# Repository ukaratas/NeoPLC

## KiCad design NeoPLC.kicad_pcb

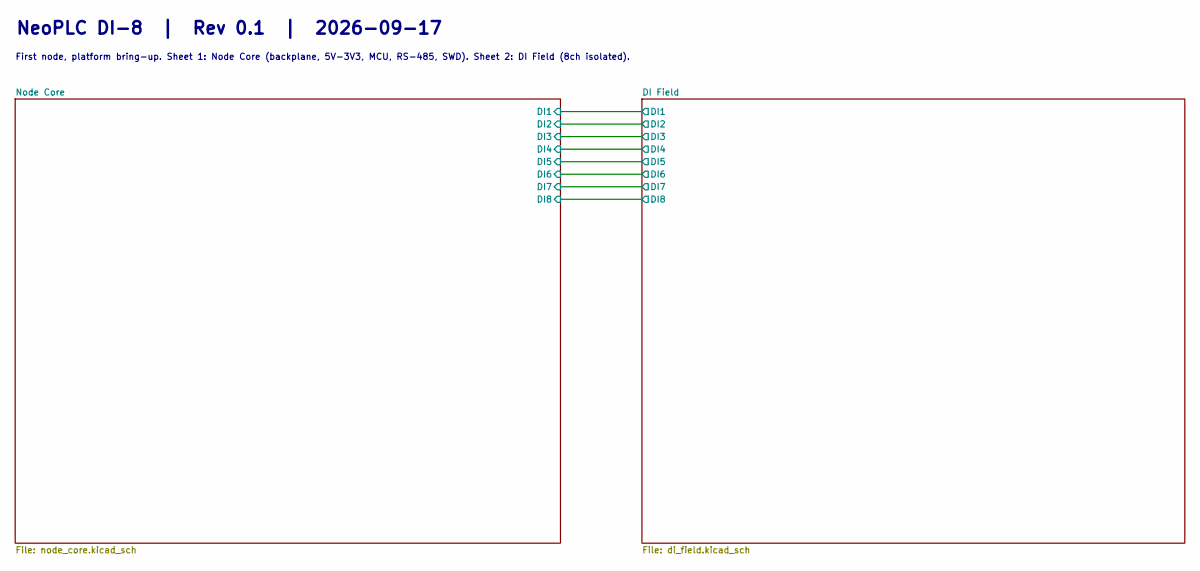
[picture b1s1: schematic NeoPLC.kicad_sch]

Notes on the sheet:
NeoPLC DI-8 | Rev 0.1 | 2026-09-17
First node, platform bring-up. Sheet 1: Node Core (backplane, 5V-3V3, MCU, RS-485, SWD). Sheet 2: DI Field (8ch isolated).

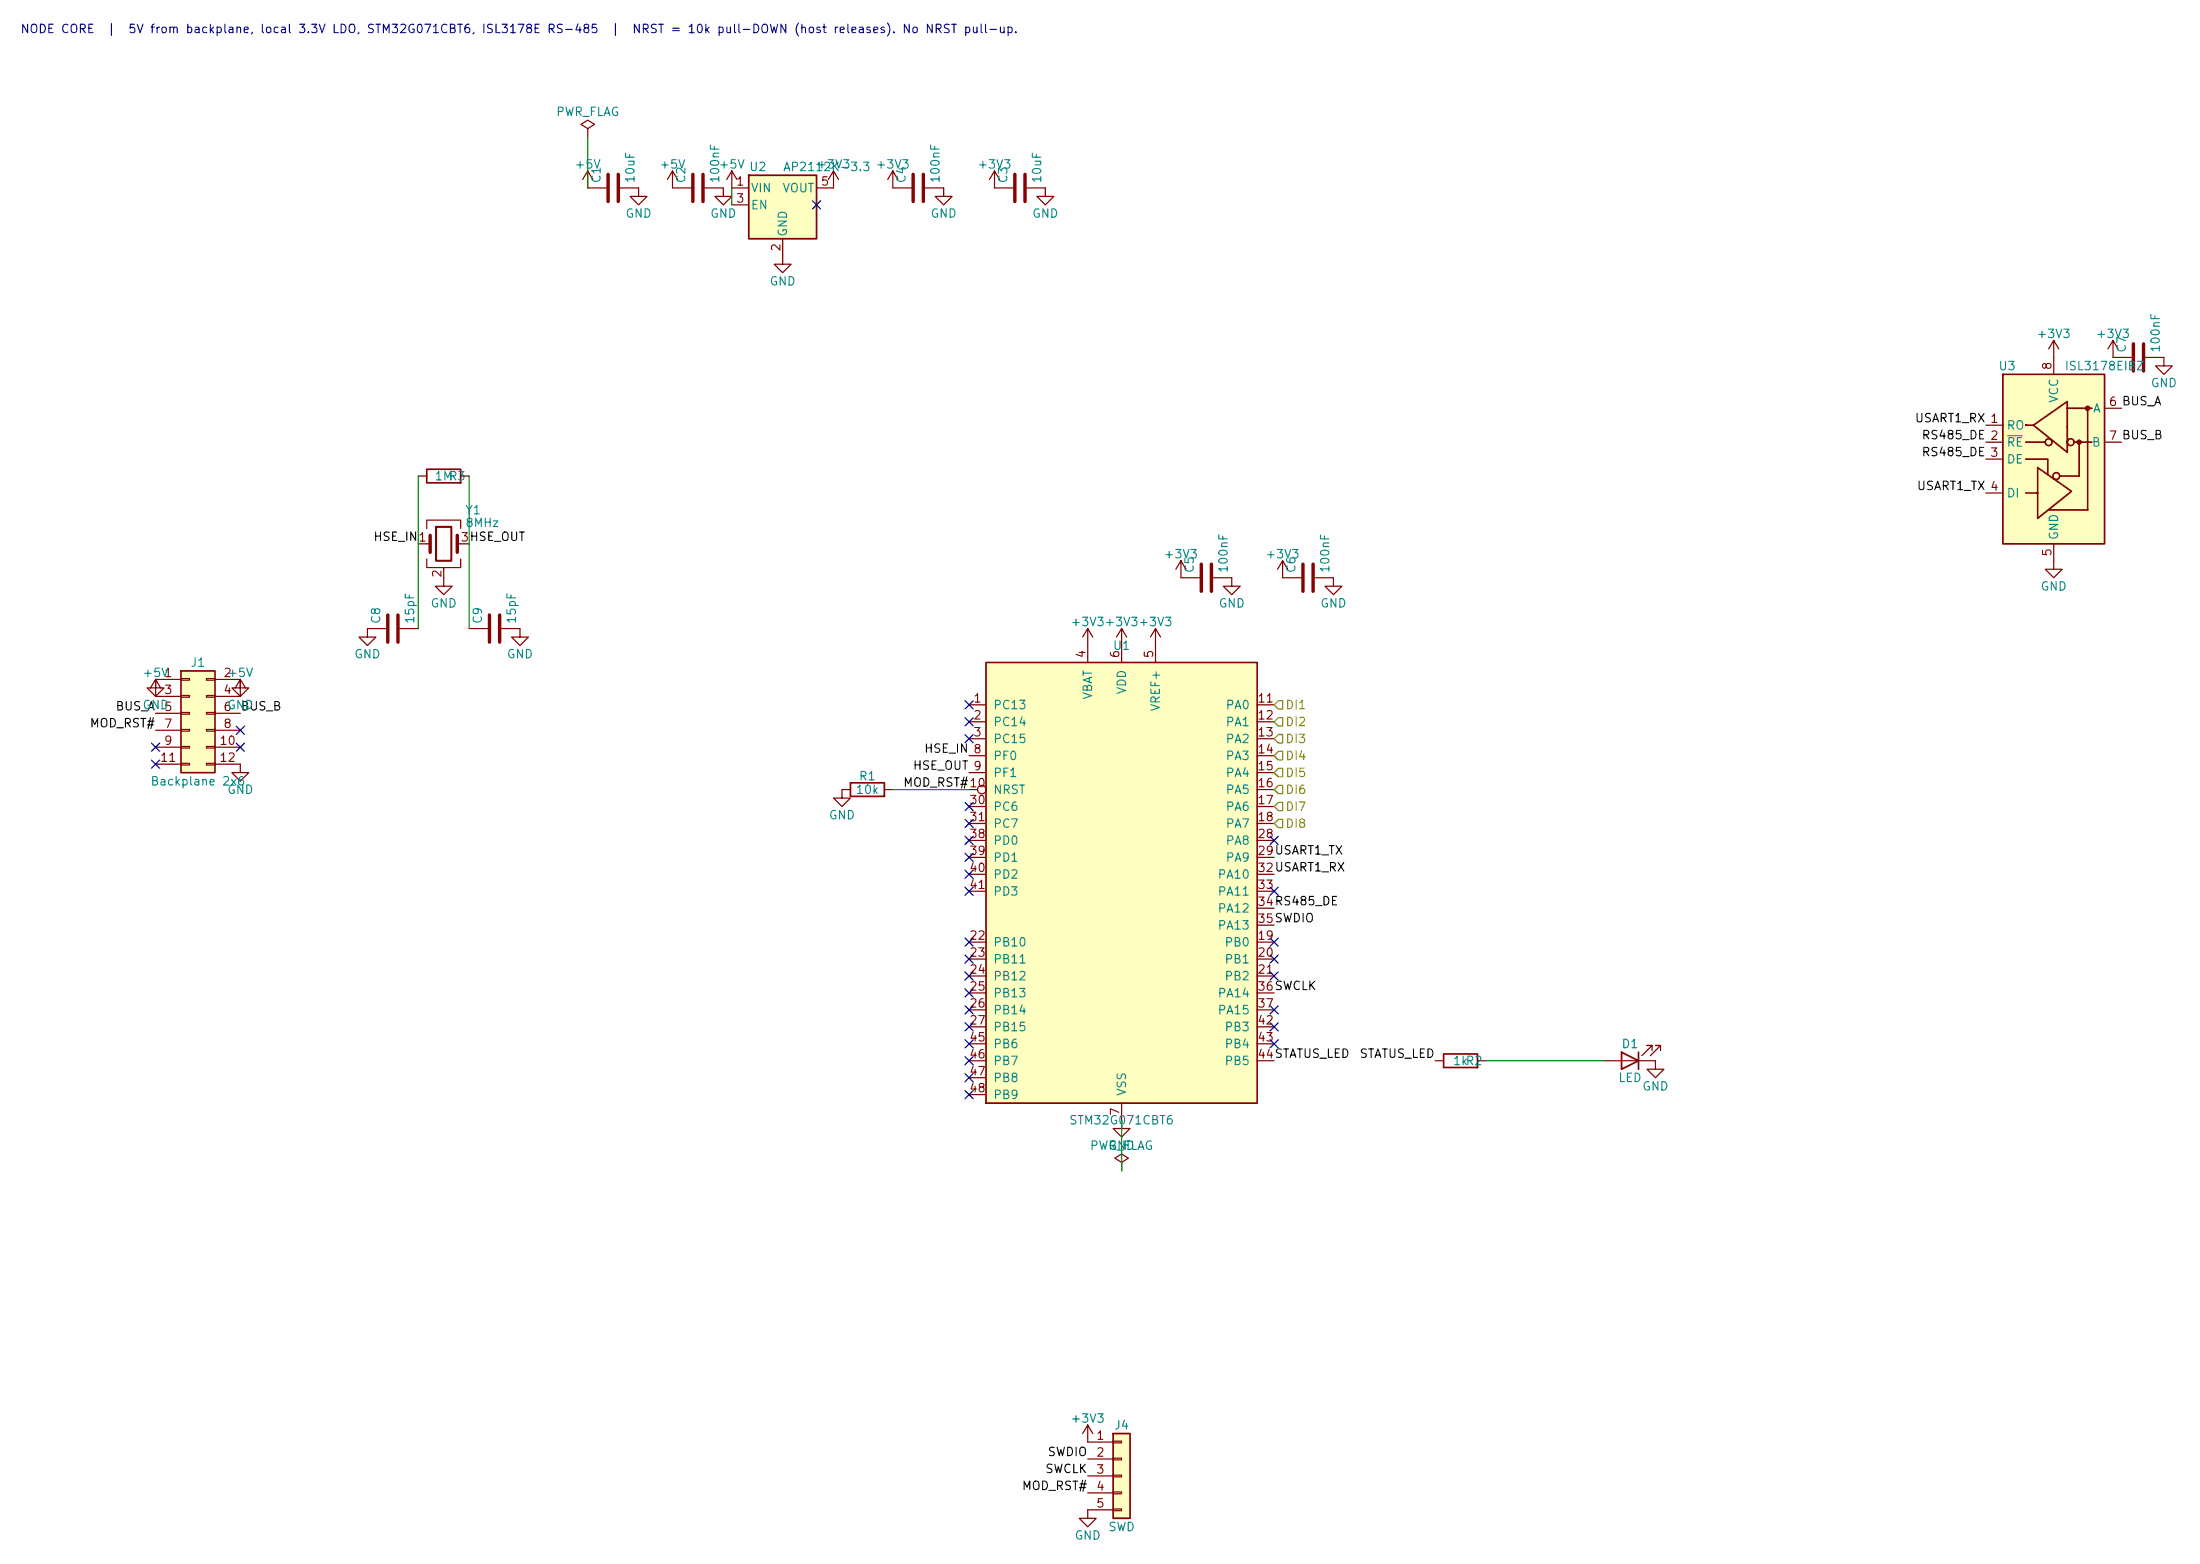
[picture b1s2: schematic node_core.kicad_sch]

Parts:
C1, C3: 10uF; C_0805_2012Metric
C2, C4, C5, C6, C7: 100nF; C_0402_1005Metric
C8, C9: 15pF; C_0402_1005Metric
D1: LED; LED_0805_2012Metric
J1: Backplane 2x6; GoldFinger_2x6_2.54
J4: SWD; PinHeader_1x05_P2.54mm_Vertical
R1: 10k; R_0402_1005Metric
R2: 1k; R_0402_1005Metric
R3: 1M; R_0402_1005Metric
U1: STM32G071CBT6; LQFP-48_7x7mm_P0.5mm; MPN STM32G071CBT6
U2: AP2112K-3.3; SOT-23-5; MPN AP2112K-3.3TRG1
U3: ISL3178EIBZ; SOIC-8_3.9x4.9mm_P1.27mm; MPN ISL3178EIBZ
Y1: 8MHz; Crystal_SMD_3225-4Pin_3.2x2.5mm

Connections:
+3V3: C3.1, C4.1, C5.1, C6.1, C7.1, J4.1, U1.4 (VBAT), U1.5 (VREF+), U1.6 (VDD), U2.5 (VOUT), U3.8 (VCC); also elsewhere on the board
/DI Field/DI1: U1.11 (PA0); also elsewhere on the board
/DI Field/DI2: U1.12 (PA1); also elsewhere on the board
/DI Field/DI3: U1.13 (PA2); also elsewhere on the board
/DI Field/DI4: U1.14 (PA3); also elsewhere on the board
/DI Field/DI5: U1.15 (PA4); also elsewhere on the board
/DI Field/DI6: U1.16 (PA5); also elsewhere on the board
/DI Field/DI7: U1.17 (PA6); also elsewhere on the board
/DI Field/DI8: U1.18 (PA7); also elsewhere on the board
/Node Core/BUS_A: J1.5, U3.6 (A)
/Node Core/BUS_B: J1.6, U3.7 (B)
/Node Core/HSE_IN: C8.2, R3.1, U1.8 (PF0), Y1.1
/Node Core/HSE_OUT: C9.1, R3.2, U1.9 (PF1), Y1.3
/Node Core/MOD_RST#: J1.7, J4.4, R1.2, U1.10 (NRST)
/Node Core/RS485_DE: U1.34 (PA12), U3.2 (~RE), U3.3 (DE)
/Node Core/STATUS_LED: R2.1, U1.44 (PB5)
/Node Core/SWCLK: J4.3, U1.36 (PA14)
/Node Core/SWDIO: J4.2, U1.35 (PA13)
/Node Core/USART1_RX: U1.32 (PA10), U3.1 (RO)
/Node Core/USART1_TX: U1.29 (PA9), U3.4 (DI)
unnamed: D1.2 (A), R2.2

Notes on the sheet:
NODE CORE | 5V from backplane, local 3.3V LDO, STM32G071CBT6, ISL3178E RS-485 | NRST = 10k pull-DOWN (host releases). No NRST pull-up.

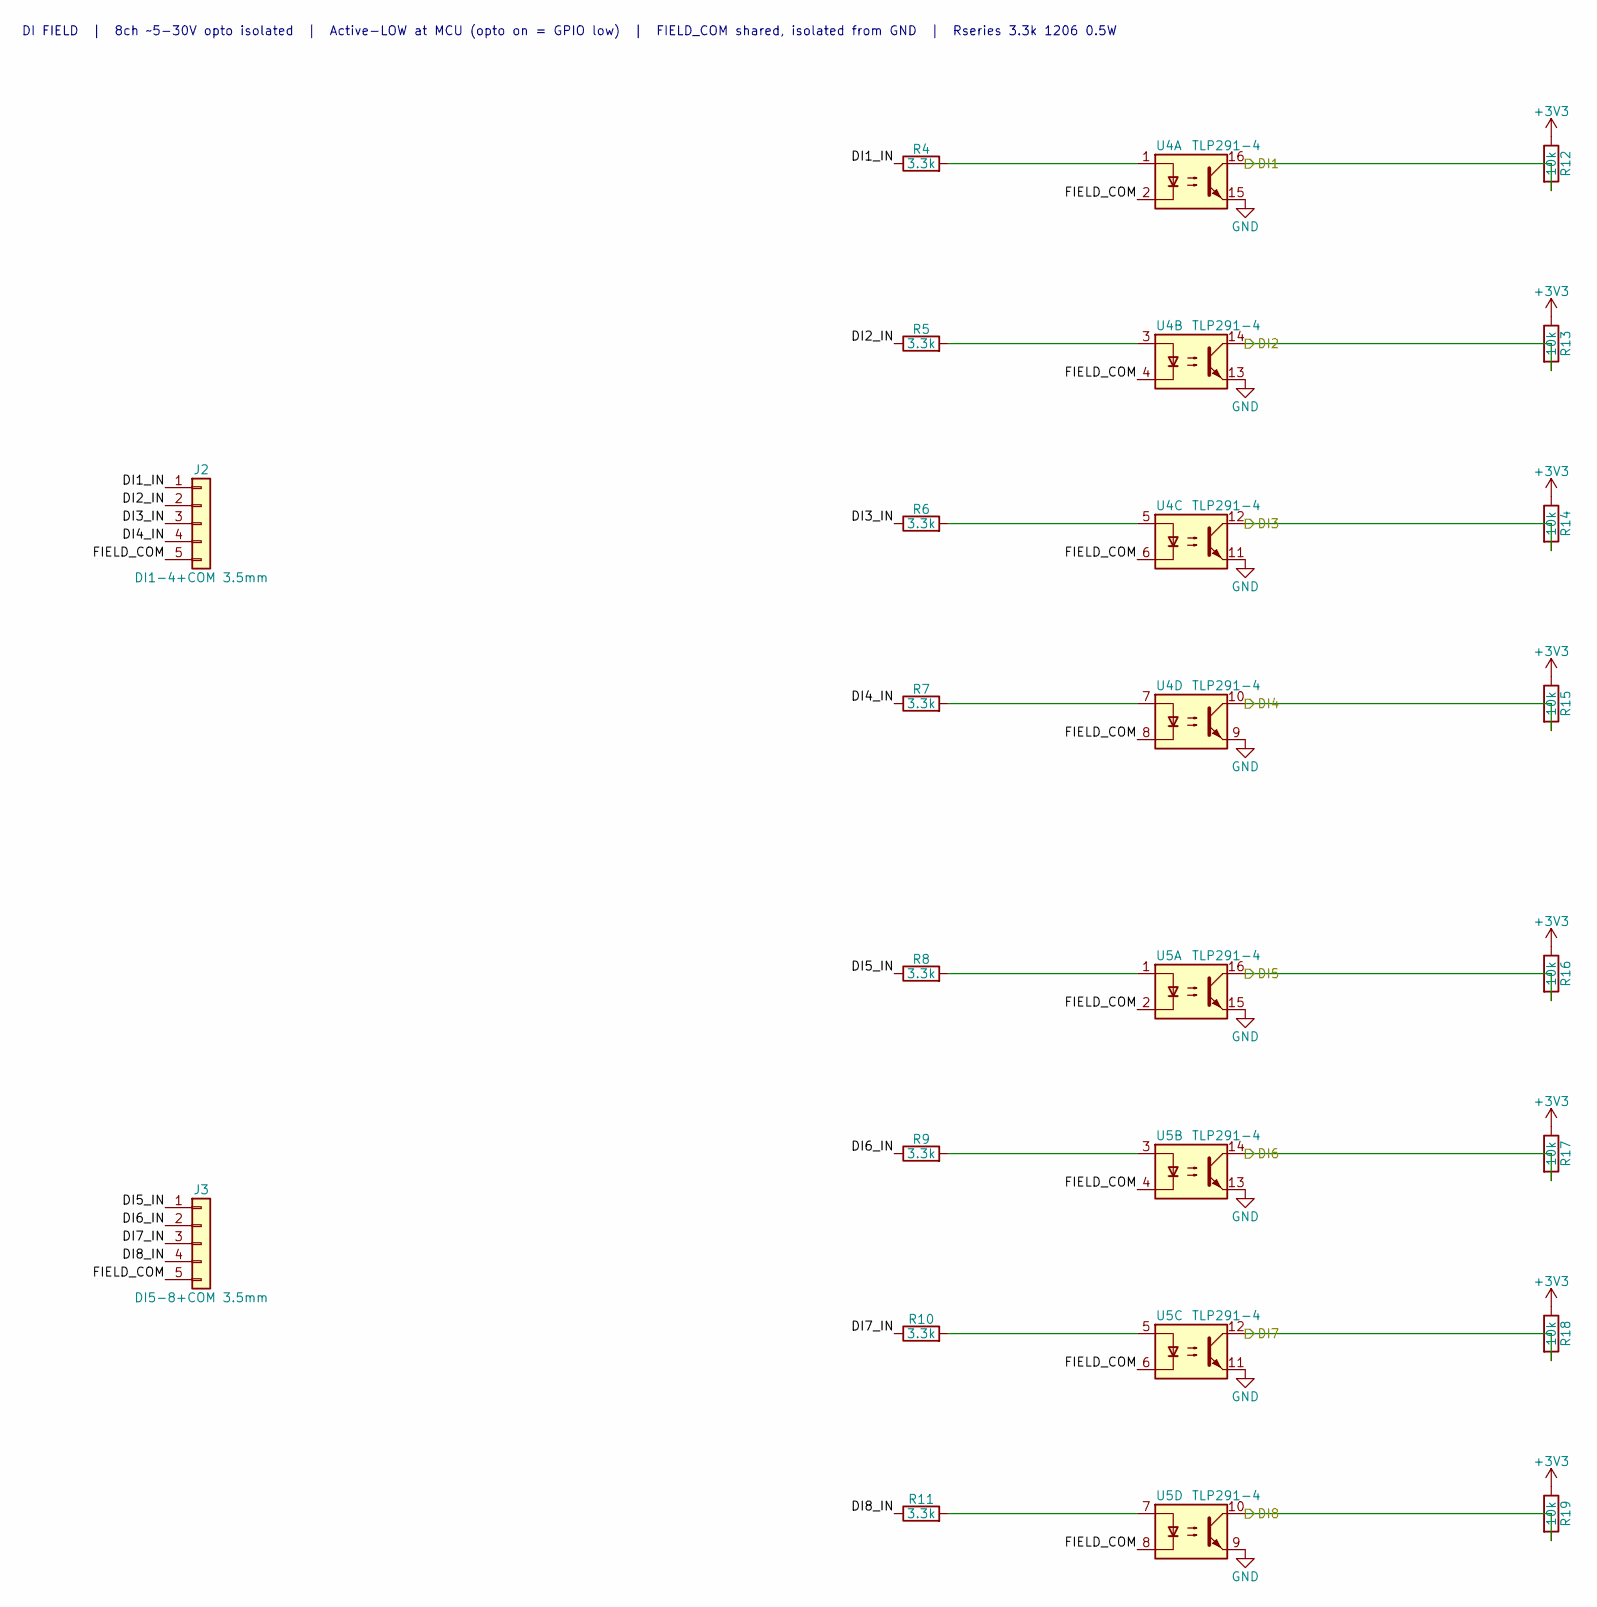
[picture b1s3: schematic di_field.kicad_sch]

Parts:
J2: DI1-4+COM 3.5mm; PhoenixContact_MCV_1,5_5-G-3.5_1x05_P3.50mm_Vertical
J3: DI5-8+COM 3.5mm; PhoenixContact_MCV_1,5_5-G-3.5_1x05_P3.50mm_Vertical
R4, R5, R6, R7, R8, R9, R10, R11: 3.3k; R_1206_3216Metric
R12, R13, R14, R15, R16, R17, R18, R19: 10k; R_0402_1005Metric
U4, U5: TLP291-4; SOIC-16_4.55x10.3mm_P1.27mm; MPN TLP291-4

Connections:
+3V3: R12.1, R13.1, R14.1, R15.1, R16.1, R17.1, R18.1, R19.1; also elsewhere on the board
/DI Field/DI1: R12.2, U4.16; also elsewhere on the board
/DI Field/DI1_IN: J2.1, R4.1
/DI Field/DI2: R13.2, U4.14; also elsewhere on the board
/DI Field/DI2_IN: J2.2, R5.1
/DI Field/DI3: R14.2, U4.12; also elsewhere on the board
/DI Field/DI3_IN: J2.3, R6.1
/DI Field/DI4: R15.2, U4.10; also elsewhere on the board
/DI Field/DI4_IN: J2.4, R7.1
/DI Field/DI5: R16.2, U5.16; also elsewhere on the board
/DI Field/DI5_IN: J3.1, R8.1
/DI Field/DI6: R17.2, U5.14; also elsewhere on the board
/DI Field/DI6_IN: J3.2, R9.1
/DI Field/DI7: R18.2, U5.12; also elsewhere on the board
/DI Field/DI7_IN: J3.3, R10.1
/DI Field/DI8: R19.2, U5.10; also elsewhere on the board
/DI Field/DI8_IN: J3.4, R11.1
/DI Field/FIELD_COM: J2.5, J3.5, U4.2, U4.4, U4.6, U4.8, U5.2, U5.4, U5.6, U5.8
unnamed: R4.2, U4.1
unnamed: R5.2, U4.3
unnamed: R6.2, U4.5
unnamed: R7.2, U4.7
unnamed: R8.2, U5.1
unnamed: R9.2, U5.3
unnamed: R10.2, U5.5
unnamed: R11.2, U5.7

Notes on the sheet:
DI FIELD | 8ch ~5-30V opto isolated | Active-LOW at MCU (opto on = GPIO low) | FIELD_COM shared, isolated from GND | Rseries 3.3k 1206 0.5W

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
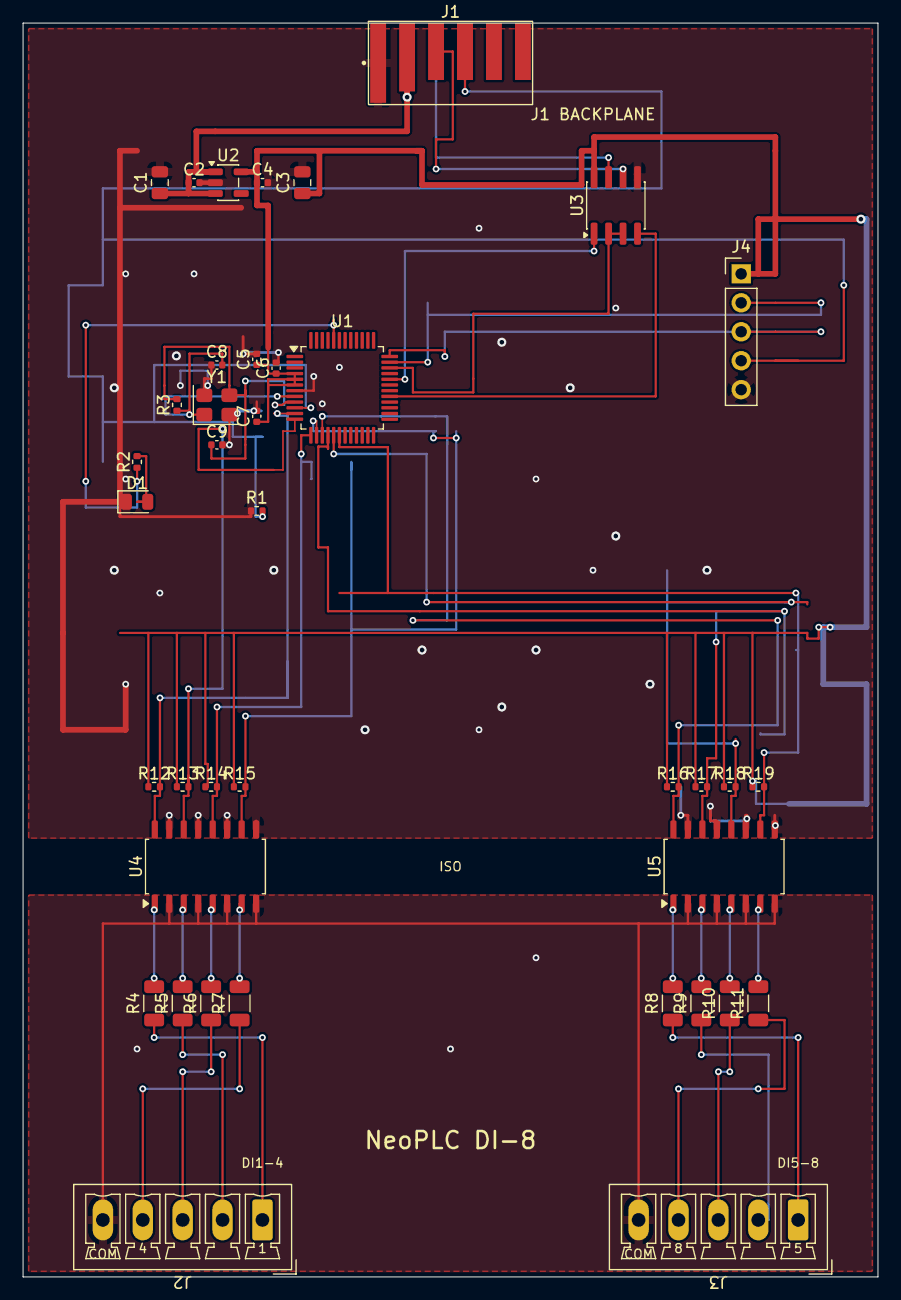
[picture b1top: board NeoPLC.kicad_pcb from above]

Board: 2 copper layers, 75.0 x 110.0 mm, 39 parts (0 on the bottom side), 40 nets.
